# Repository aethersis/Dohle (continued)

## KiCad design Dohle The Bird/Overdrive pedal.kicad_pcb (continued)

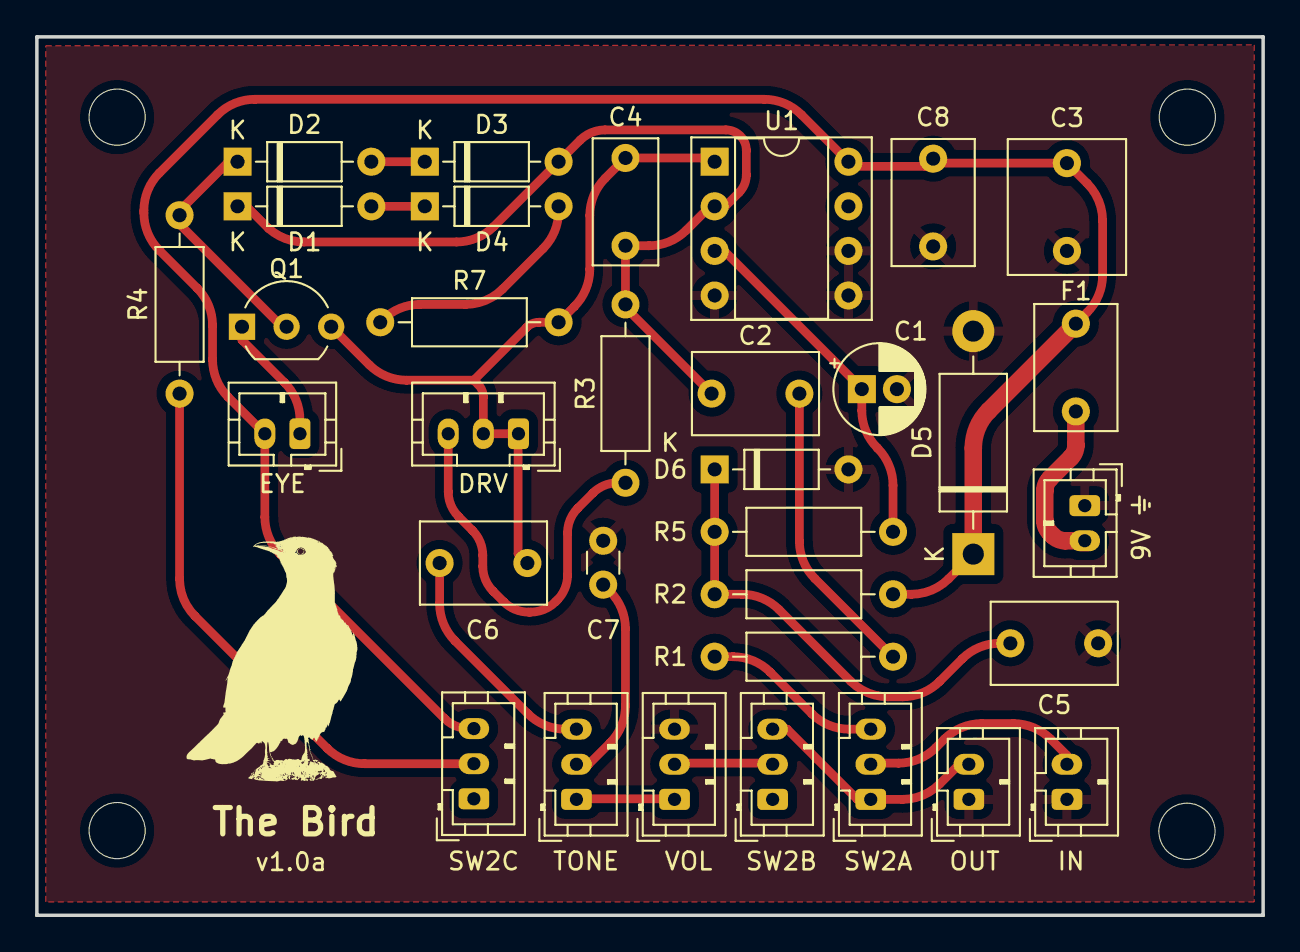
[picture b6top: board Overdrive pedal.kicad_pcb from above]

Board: 2 copper layers, 69.8 x 50.0 mm, 37 parts (0 on the bottom side), 22 nets.

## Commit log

2022-07-09 Add the ray pedal
2022-07-09 Add the bird pedal
2022-07-12 Add the howler and string maschine
2022-07-12 Update the ray footswitch footprint
2022-07-12 Add missing gitignore file
2022-07-12 Update StringMaschine with level shifters
2022-07-15 Add opamp rail splitter
2022-07-19 Add DAC
2022-07-20 Add keytar control board
2022-07-20 Adapt the keytar to use VCA
2022-07-21 Strin Maschine - first revision before review
2022-07-21 String Maschine - assign symbols
2022-07-21 String Maschine - fix VCF range
2022-07-22 String Maschine controller - fix broken symbols
2022-07-24 String Maschine - Add simulations and add VCA for controlling the feedback loop
2022-07-24 String Maschine - finish voice board
2022-07-24 String Maschine - Fix pentanoise symbol
